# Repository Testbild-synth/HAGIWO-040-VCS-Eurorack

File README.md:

# HAGIWO-040-VCS-Eurorack

Through-hole PCB version of the [HAGIWO 040 Select Voltage controlled Switch Eurorack module](https://www.youtube.com/watch?v=aYyemBHd6mM) .
The module is basically built around an analog switch IC that allows you to direct one channel of a signal in one of two "output channels" depending on button presses or a control voltage.

I made the change to switch the IC to a DG211/DG411, since those are far more available to me. I also made the change to replace the threshold potentiometer in the front with a trimmer in the back, but also the trimmers are unique for each channel.

### STATUS: Now on version 4 with improved spacing on the panel and pcb. 

## PCB and Hardware

You can find the schematic and BOM in the root folder. 
For the PCBs, the module has one circuit PCB and one panel PCB. You can order them on any common PCB manufacturing service, I used JLCPCB. Standard settings should be fine.

Probably the only part that is a bit special about the BOM in this are the switches: I made the choice to switch the standard push switches HAGIWO uses to CHERRY MX switches.
They are bigger, sure, but they are also far more satisfying and everyone can [insert their favourite type](https://switchandclick.com/wp-content/uploads/2020/07/Cherry-MX-Switch-Guide-1-1024x679.webp), I vote for clicky blues! Make sure to get the "RGB" option which has space for the LED indicator. I got the wrong ones and had to kinda bend the bottom of mine to make the LED fit.

For the build, the PCB is very crowded since i tried to fit everything on one PCB. in former revisions there was a problem with jack spacing, but this has been solved. for earlier versions see the commit history.

## Tuning
The module has two trimpots which you can use to set the trigger voltage for each channel. The easiest way to set these imo is to feed it the voltage you want (say 2.5V) and then adjust the trimpot until the point where it barely triggers a channel change. I have mine set to different voltages (1V and 2V) so that I can feed the same lfo into both and get different timing from it, but do as you prefer!

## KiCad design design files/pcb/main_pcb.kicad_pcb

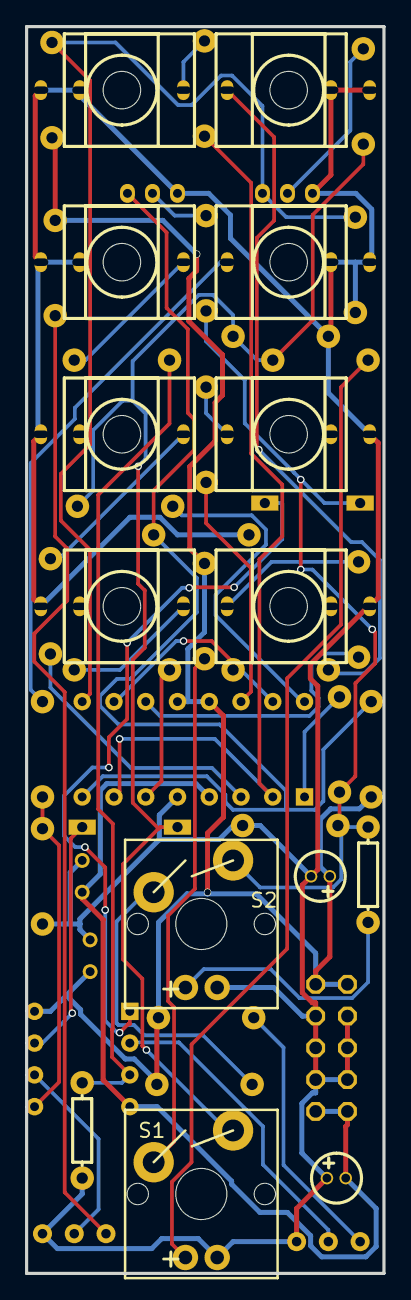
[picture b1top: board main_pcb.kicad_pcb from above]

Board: 2 copper layers, 28.6 x 99.7 mm, 49 parts (0 on the bottom side), 37 nets.

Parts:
C1, C2: 100n; RAD-0.1
C3, C4: 10u; CAP-D4.0×F1.5
D1, D2: 1n4148; DO35-7
EP1: EURORACK_POWERHEADER_V2; EURORACK_POWER_V2
J1: IOA; THONKICONN_1
J2: IOA1; THONKICONN_1
J3: IOA2; THONKICONN_1
J4: IOB; THONKICONN_1
J5: IOB1; THONKICONN_1
J6: IOB2; THONKICONN_1
J7: CVA; THONKICONN_1
J8: CVB; THONKICONN_1
R1, R2, R5, R6, R7, R8: 470; R_AXIAL-0.3
R3, R4, R9, R18: 1k; R_AXIAL-0.3
R10, R11, R12, R13, R14, R15, R16, R19, R20, R21, R22, R23, R24, R25: 10k; R_AXIAL-0.3
R17, R26: 33k; R_AXIAL-0.3
S1: MOMENTARY-SWITCH-SPST-LED-PTH-CHERRY; CHERRY-MX-LED
S2: CHERRY_SW; CHERRY-MX-LED
THRESH1, THRESH2: 10k; TRIMPOT
U1: TL072BCP; DIP8
U2: DG211CJ; DIP16
U3, U4: BC547; BC547 OH

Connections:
12V: C2.1, C4.1, EP1.12, R3.1, R4.1, R15.1, R16.2, R24.1, R25.2, U1.8, U2.12, U2.13
-12V: C1.1, C3.2, EP1.-12, U1.4, U2.4
GND: C1.2, C2.2, C3.1, C4.2, EP1.GND0, EP1.GND1, EP1.GND2, EP1.GND3, EP1.GND4, EP1.GND5, J1.1, J1.2, J2.1, J3.1, J4.1, J4.2, J5.1, J6.1, J7.1, J7.2, J8.1, J8.2, R11.2, R12.2, R17.1, R20.2, R21.2, R26.1, S1.K, S2.K, THRESH1.3, THRESH2.3, U2.5, U3.3, U4.3
IC_1: R10.2, U2.1
IC_3: R2.1, U2.3
IC_6: R5.1, U2.6
IC_8: R16.1, R17.2, U2.8, U3.1
IC_9: R25.1, R26.2, U2.9, U4.1
IC_11: R8.1, U2.11
IC_14: R7.1, U2.14
IC_16: R19.2, U2.16
IOA: R1.2, U2.2, U2.7
IOB: R6.2, U2.10, U2.15
J1_3: J1.3, R1.1
J3_3: J3.3, R5.2
J5_3: J5.3, R7.2
J7_3: J7.3, R9.2
LED1: R13.2, S2.A
LED2: R22.2, S1.A
R2_2: J2.3, R2.2
R4_2: R4.2, S2.S1
R6_1: J4.3, R6.1
R8_2: J6.3, R8.2
R9_1: R9.1, R11.1, U1.3
R14_1: R14.1, U3.2
R18_2: J8.3, R18.2
R24_2: R24.2, THRESH2.1
S1_S1: R3.2, S1.S1
SW1: D1.C, R10.1, R12.1, R13.1, R14.2, S2.S2
SW2: D2.C, R19.1, R21.1, R22.1, R23.2, S1.S2
THRESH1_1: R15.2, THRESH1.1
U1_1: D1.A, U1.1
U1_2: THRESH1.2, U1.2
U1_5: R18.1, R20.1, U1.5
U1_6: THRESH2.2, U1.6
U1_7: D2.A, U1.7
U4_2: R23.1, U4.2

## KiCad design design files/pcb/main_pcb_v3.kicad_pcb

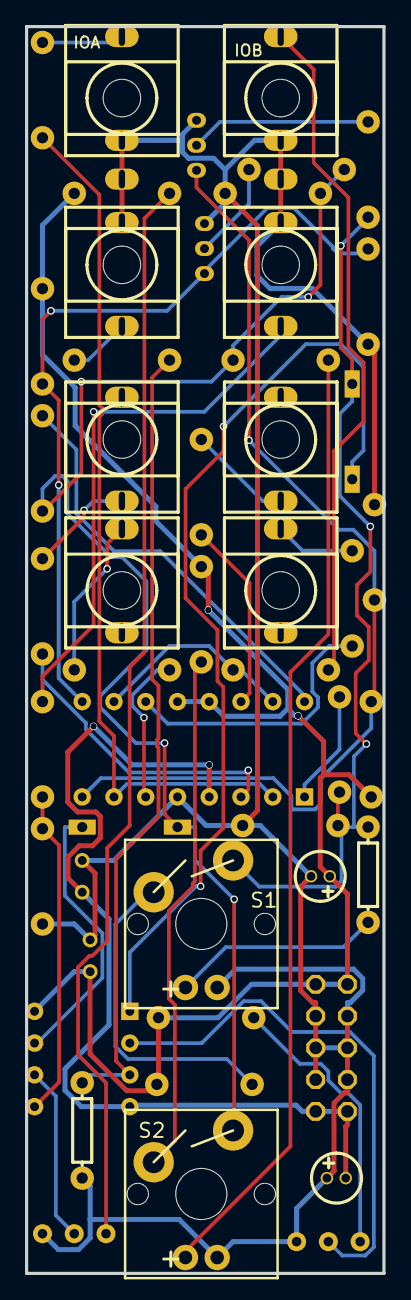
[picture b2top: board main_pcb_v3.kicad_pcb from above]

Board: 2 copper layers, 28.6 x 99.7 mm, 41 parts (0 on the bottom side), 29 nets.

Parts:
C1, C6: 100n; RAD-0.1
C5, C7: 10u; CAP-D4.0×F1.5
D1, D2: 1n4148; DO35-7
EP1: EURORACK_POWERHEADER_V2; EURORACK_POWER_V2
R1, R2, R3, R4, R6, R7, R9, R18, R19, R20, R21, R22, R23, R24: 10k; R_AXIAL-0.3
R5, R8, R25, R26: 1k; R_AXIAL-0.3
R10, R17: 33k; R_AXIAL-0.3
R11, R12, R13, R14, R15, R16: 470; R_AXIAL-0.3
S1, S2: +; CHERRY-MX-LED
THRESH1, THRESH2: 10k; TRIMPOT
U1: DG211CJ; DIP16
U2: TL072; DIP8
U3, U4: BC547; BC547 OH

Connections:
12V: C1.1, C7.1, EP1.12, R2.1, R5.1, R9.2, R18.2, R23.1, R26.1, U1.12, U1.13, U2.8
-12V: C5.2, C6.1, EP1.-12, U1.4, U2.4
GND: C1.2, C5.1, C6.2, C7.2, EP1.GND0, EP1.GND1, EP1.GND2, EP1.GND3, EP1.GND4, EP1.GND5, R1.2, R3.2, R10.1, R17.1, R22.2, R24.2, S1.K, S2.K, THRESH1.3, THRESH2.3, U1.5, U3.3, U4.3
IC_1: R6.2, U1.1
IC_3: R12.1, U1.3
IC_6: R13.1, U1.6
IC_8: R9.1, R10.2, U1.8, U3.1
IC_9: R17.2, R18.1, U1.9, U4.1
IC_11: R15.1, U1.11
IC_14: R16.1, U1.14
IC_16: R20.2, U1.16
IOA: R11.2, U1.2, U1.7
IOB: R14.2, U1.10, U1.15
LED1: R4.2, S1.A
LED2: R21.2, S2.A
R5_2: R5.2, S1.S1
R7_1: R7.1, U3.2
R8_1: R1.1, R8.1, U2.3
R23_2: R23.2, THRESH2.1
S2_S1: R26.2, S2.S1
SW1: D1.C, R3.1, R4.1, R6.1, R7.2, S1.S2
SW2: D2.C, R19.2, R20.1, R21.1, R22.1, S2.S2
THRESH1_1: R2.2, THRESH1.1
U2_1: D1.A, U2.1
U2_2: THRESH1.2, U2.2
U2_5: R24.1, R25.1, U2.5
U2_6: THRESH2.2, U2.6
U2_7: D2.A, U2.7
U4_2: R19.1, U4.2

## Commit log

2022-02-03 created folder structure and uploaded panel design files
2022-02-03 uploaded gerbers and design files for main pcb
2022-02-03 Added bom and schematic
2022-02-08 v2 pcb and panel, since jlc complained because of cutout dimensions
2022-02-08 fixed an error with the panel pcb gerber
2022-03-14 fixed a grounding issue with previous version
2022-03-14 image upload
2022-03-14 image update
2022-10-04 v4 better spacing
2022-10-04 new images for v4
2023-09-11 fixed botched kicad export
